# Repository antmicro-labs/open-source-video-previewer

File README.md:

# open-source-video-previewer
Project purpose
Developing video in/out overlay device, that will be able to record, process, stream further and allow to modificate processing parameters.

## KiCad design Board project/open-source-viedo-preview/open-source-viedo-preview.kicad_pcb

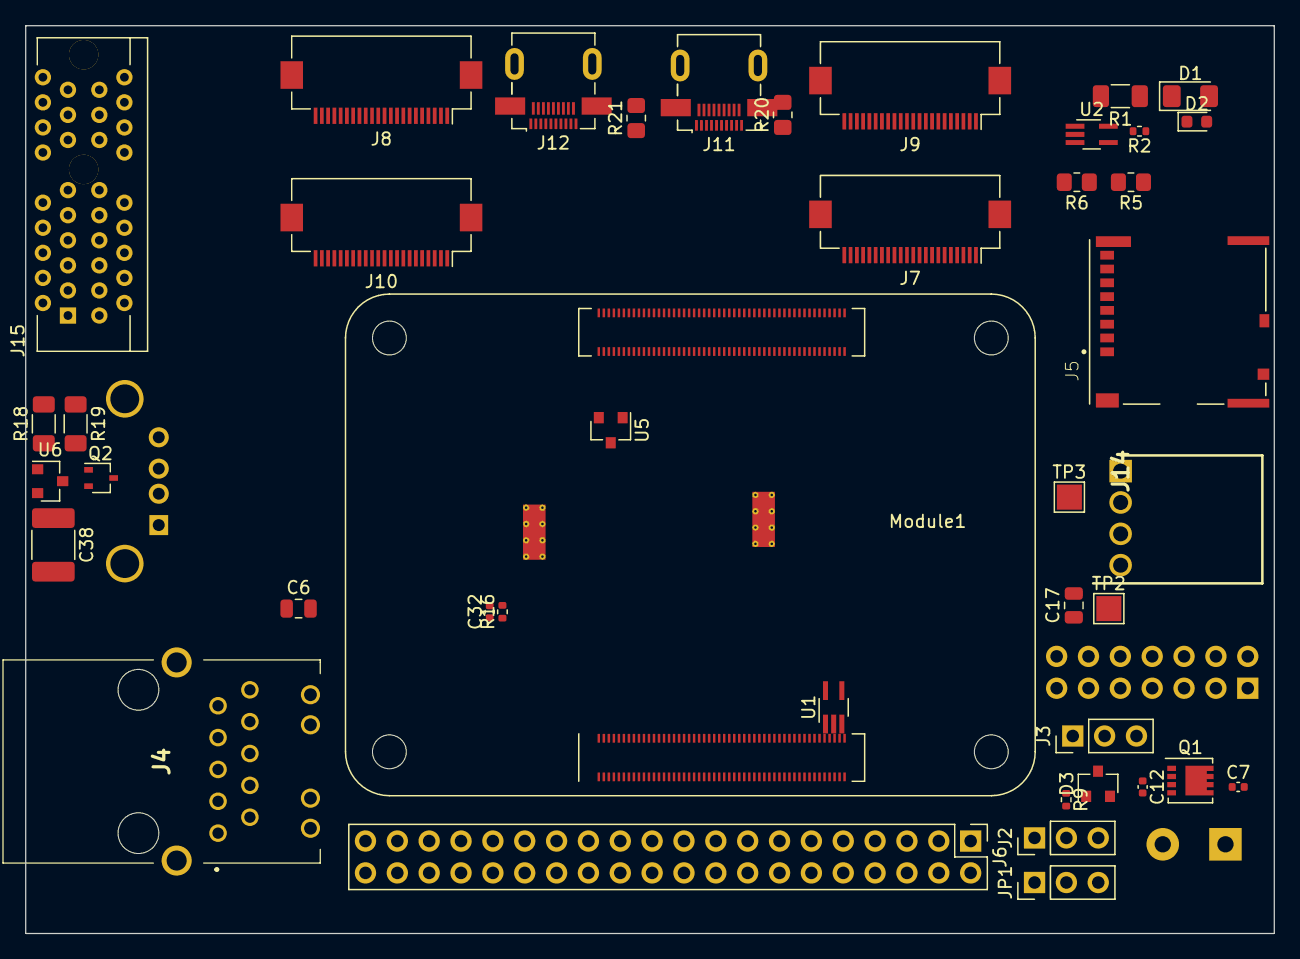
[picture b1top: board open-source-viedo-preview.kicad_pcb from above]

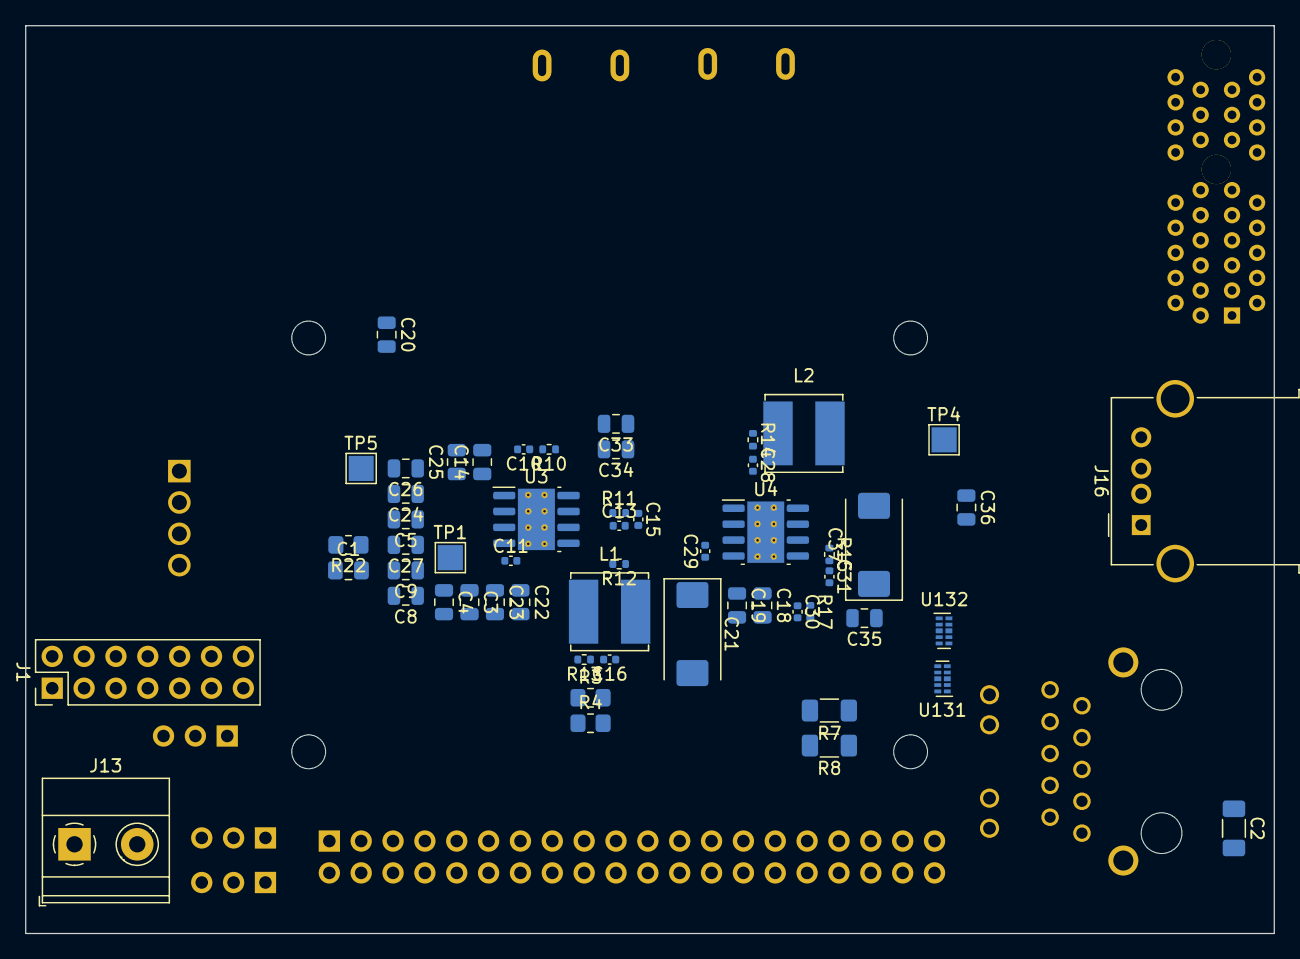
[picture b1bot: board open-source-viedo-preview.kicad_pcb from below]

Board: 4 copper layers, 99.6 x 72.4 mm, 98 parts (56 on the bottom side), 145 nets, no tracks yet.

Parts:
C1: 10u; C_0805_2012Metric_Pad1.18x1.45mm_HandSolder
C2: 10n; C_1206_3216Metric_Pad1.33x1.80mm_HandSolder
C3, C4, C5, C6, C8, C9, C14, C22, C23, C24, C25, C26, C27: 10u 35v; C_0805_2012Metric
C7: 100n 100v; C_0402_1005Metric
C10, C11, C12, C28, C29: 100n; C_0402_1005Metric
C13, C16, C30, C32: nf; C_0402_1005Metric
C15, C31: 1.2nF; C_0402_1005Metric
C17, C18, C19, C20, C33, C34, C35, C36: 10u; C_0805_2012Metric
C21, C37: 100uF; CP_EIA-7343-31_Kemet-D
C38: 4u7; C_1812_4532Metric_Pad1.57x3.40mm_HandSolder
D1: Green LED; LED_1206_3216Metric_Pad1.42x1.75mm_HandSolder
D2: LED Red; LED_0603_1608Metric
D3: MMBZ5242BLT3G; D_SOT-23_ANK
J1: Conn_02x07_Odd_Even; PinHeader_2x07_P2.54mm_Vertical
J2, J3: Conn_01x03; PinHeader_1x03_P2.54mm_Vertical
J4: 7499110124
J5: Micro_SD_Card_Det; SDCARD_MOLEX_503398-1892
J6: Conn_02x20_Odd_Even; PinHeader_2x20_P2.54mm_Vertical
J7, J8, J9, J10: Conn_01x22_Female; Hirose_FH12-22S-0.5SH_1x22-1MP_P0.50mm_Horizontal
J11, J12: HDMI_A_1.4; HDMI_Micro-D_Molex_46765-2x0x
J13: Screw_Terminal_01x02; TerminalBlock_Phoenix_MKDS-1,5-2_1x02_P5.00mm_Horizontal
J14: AMP171826-4; SHDRRA4W69P0X250_1X4_1000X1350X670P
J15: 10018783-11200TLF; PCIex1-36
J16: USB_OTG; USB_A_Molex_67643_Horizontal
JP1: Jumper_NC_Dual; PinHeader_1x03_P2.54mm_Vertical
L1, L2: SRN6045TA-3R3Y; L_Bourns_SRN6045TA
Module1: ComputeModule4-CM4; Raspberry-Pi-4-Compute-Module
Q1: DMP3013SFV-7; Diodes_PowerDI3333-8
Q2: BSS138PW; SOT-323_SC-70
R1: 1k; R_1206_3216Metric_Pad1.30x1.75mm_HandSolder
R2: 1k; R_0402_1005Metric
R3, R4: 1k8; R_0805_2012Metric_Pad1.20x1.40mm_HandSolder
R5, R6: R; R_0805_2012Metric_Pad1.20x1.40mm_HandSolder
R7, R8: 220; R_1206_3216Metric_Pad1.30x1.75mm_HandSolder
R9, R12, R15: 12K 1%; R_0402_1005Metric
R10, R14: 10R; R_0402_1005Metric
R11: 20K 1%; R_0402_1005Metric
R13: 2.2K 1%; R_0402_1005Metric
R16: 47K 1%; R_0402_1005Metric
R17: 15K 1%; R_0402_1005Metric
R18: 10k; R_1206_3216Metric_Pad1.30x1.75mm_HandSolder
R19: 2k; R_1206_3216Metric_Pad1.30x1.75mm_HandSolder
R20, R21, R22: 0R; R_0805_2012Metric_Pad1.20x1.40mm_HandSolder
TP1, TP2, TP3, TP4, TP5: TestPoint; TestPoint_Pad_2.0x2.0mm
U1, U2: 74LVC1G07; SOT-353_SC-70-5_Handsoldering
U3, U4: AP64501SP-13; SOIC-8-1EP_3.9x4.9mm_P1.27mm_EP2.95x4.9mm_Mask2.71x3.4mm_Th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
U5, U6: TPD2E009DBZR; SOT-23
U131, U132: TPD4EUSB30; USON-10_2.5x1.0mm_P0.5mm

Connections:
+1V8: JP1.3, Module1.88 (+1.8v_(Output)), Module1.90 (+1.8v_(Output))
+3V3: C16.1, C17.1, C18.1, C19.1, C20.1, C21.1, D1.2 (A), D2.2 (A), J6.1, J6.2, J6.4, J6.7, J6.17, J7.22, J8.22, J9.22, J10.22, J14.4, JP1.1, L1.2, Module1.54 (GPIO4), Module1.77 (+5v_(Input)), Module1.79 (+5v_(Input)), Module1.81 (+5v_(Input)), Module1.83 (+5v_(Input)), Module1.84 (+3.3v_(Output)), Module1.85 (+5v_(Input)), Module1.86 (+3.3v_(Output)), Module1.87 (+5v_(Input)), R5.1, R7.2, R8.2, R12.1, R20.1, R21.1, R22.1, TP2.1, U1.5 (VCC), U2.5 (VCC)
+12V: C3.1, C4.1, C5.1, C6.1, C8.1, C9.1, C12.1, C14.1, C22.1, C23.1, C24.1, C25.1, C26.1, C27.1, D3.1 (K), J14.1, J15.A2 (+12V), J15.A3 (+12V), J15.B1 (+12v), J15.B2 (+12v), J15.B3 (+12v), Q1.1 (S), Q1.2 (S), Q1.3 (S), TP1.1, U3.2 (VIN), U3.3 (EN), U4.2 (VIN), U4.3 (EN)
/pcie/+3.3v: C32.1, C33.1, C34.1, C35.1, C36.1, C37.1, J15.A5 (TCK), J15.A6 (TDI), J15.A8 (TMS), J15.A9 (+3.3V), J15.A10 (+3.3V), J15.B8 (+3.3v), J15.B9 (nTRST), J15.B10 (+3.3vAUX), L2.2, R16.1, TP4.1
/pcie/PCIE_CLK_N: J15.A14 (REFCLK-), Module1.112 (PCIe_CLK_N)
/pcie/PCIE_CLK_P: J15.A13 (REFCLK+), Module1.110 (PCIe_CLK_P)
/pcie/PCIE_CLK_nREQ: J15.B12 (nCLKREQ), Module1.102 (PCIe_CLK_nREQ)
/pcie/PCIE_RX_N: J15.A16 (PERP0), Module1.118 (PCIe_RX_N)
/pcie/PCIE_RX_P: J15.A17 (PERN0), Module1.116 (PCIe_RX_P)
/pcie/PCIE_TX_N: J15.B14 (PETP0), Module1.124 (PCIe_TX_N)
/pcie/PCIE_TX_P: J15.B15 (PETN0), Module1.122 (PCIe_TX_P)
/pcie/PCIE_nRST: J15.A11 (nPERST), Module1.109 (PCIe_nRST)
/usb-otg/USB2_N: J16.2 (D-), Module1.103 (USB2_N), U5.2 (D-)
/usb-otg/USB2_P: J16.3 (D+), Module1.105 (USB2_P), U5.1 (D+)
/usb-otg/USBOTG: Module1.101 (USB_OTG_ID), Q2.3 (D)
/video_previewGPIO/AIN0: J1.5, Module1.94 (AnalogIP0)
/video_previewGPIO/AIN1: J1.6, Module1.96 (AnalogIP1)
/video_previewGPIO/BT_nDis: J2.3, Module1.91 (BT_nDisable)
/video_previewGPIO/CAM_GPIO: J7.17, J8.17, Module1.97 (Camera_GPIO)
/video_previewGPIO/EEPROM_nWP: J1.4, Module1.20 (EEPROM_nWP)
/video_previewGPIO/ETH_LED0: J4.12 (K_GREEN), Module1.15 (Ethernet_nLED3(3.3v))
/video_previewGPIO/ETH_LED1: J4.14 (A/K_GREEN/YELLOW_2), Module1.17 (Ethernet_nLED2(3.3v))
/video_previewGPIO/ETH_TRD0_N: J4.1 (D0-), Module1.10 (Ethernet_Pair0_N), U131.2 (D1-)
/video_previewGPIO/ETH_TRD0_P: J4.2 (D0+), Module1.12 (Ethernet_Pair0_P), U131.1 (D1+)
/video_previewGPIO/ETH_TRD1_N: J4.3 (D1-), Module1.6 (Ethernet_Pair1_N), U131.5 (D2-)
/video_previewGPIO/ETH_TRD1_P: J4.4 (D1+), Module1.4 (Ethernet_Pair1_P), U131.4 (D2+)
/video_previewGPIO/ETH_TRD2_N: J4.7 (D2-), Module1.9 (Ethernet_Pair2_N), U132.2 (D1-)
/video_previewGPIO/ETH_TRD2_P: J4.8 (D2+), Module1.11 (Ethernet_Pair2_P), U132.1 (D1+)
/video_previewGPIO/ETH_TRD3_N: J4.9 (D3-), Module1.5 (Ethernet_Pair3_N), U132.5 (D2-)
/video_previewGPIO/ETH_TRD3_P: J4.10 (D3+), Module1.3 (Ethernet_Pair3_P), U132.4 (D2+)
/video_previewGPIO/GLOBAL_EN: J1.14, J3.1, Module1.99 (Global_EN)
/video_previewGPIO/GPIO2: J6.3, Module1.58 (GPIO2)
/video_previewGPIO/GPIO3: J6.5, Module1.56 (GPIO3)
/video_previewGPIO/GPIO5: J6.29, Module1.34 (GPIO5)
/video_previewGPIO/GPIO8: J6.24, Module1.39 (GPIO8)
/video_previewGPIO/GPIO9: J6.21, Module1.40 (GPIO9)
/video_previewGPIO/GPIO10: J6.19, Module1.44 (GPIO10)
/video_previewGPIO/GPIO11: J6.23, Module1.38 (GPIO11)
/video_previewGPIO/GPIO12: J6.32, Module1.31 (GPIO12)
/video_previewGPIO/GPIO13: J6.33, Module1.28 (GPIO13)
/video_previewGPIO/GPIO17: J6.11, Module1.50 (GPIO17)
/video_previewGPIO/GPIO19: J6.35, Module1.26 (GPIO19)
/video_previewGPIO/GPIO20: J6.38, Module1.27 (GPIO20)
/video_previewGPIO/GPIO23: J6.16, Module1.47 (GPIO23)
/video_previewGPIO/GPIO24: J6.18, Module1.45 (GPIO24)
/video_previewGPIO/GPIO25: J6.22, Module1.41 (GPIO25)
/video_previewGPIO/GPIO26: J6.37, Module1.24 (GPIO26)
/video_previewGPIO/GPIO27: J6.13, Module1.48 (GPIO27)
/video_previewGPIO/GPIO_VREF: JP1.2, Module1.78 (GPIO_VREF(1.8v/3.3v_Input)), R3.1, R4.1
/video_previewGPIO/ID_SC: J6.28, Module1.35 (ID_SC), R4.2
/video_previewGPIO/ID_SD: J6.27, Module1.36 (ID_SD), R3.2
/video_previewGPIO/RUN_PG: J3.3, Module1.92 (RUN_PG), U1.2
/video_previewGPIO/Reserved: Module1.76 (Reserved), R6.1
/video_previewGPIO/SCL0: J8.20, J9.20, Module1.80 (SCL0)
/video_previewGPIO/SDA0: J8.21, J9.21, Module1.82 (SDA0)
/video_previewGPIO/SD_CLK: J5.5 (CLK), Module1.57 (SD_CLK)
/video_previewGPIO/SD_CMD: J5.3 (CMD), Module1.62 (SD_CMD)
/video_previewGPIO/SD_DATA0: J5.7 (DAT0), Module1.63 (SD_DAT0)
/video_previewGPIO/SD_DATA1: J5.8 (DAT1), Module1.67 (SD_DAT1)
/video_previewGPIO/SD_DATA2: J5.1 (DAT2), Module1.69 (SD_DAT2)
/video_previewGPIO/SD_DATA3: J5.2 (DAT3/CD), Module1.61 (SD_DAT3)
/video_previewGPIO/SYNC_IN: J1.8, Module1.16 (Ethernet_SYNC_IN(1.8v))
/video_previewGPIO/SYNC_OUT: J1.9, Module1.18 (Ethernet_SYNC_OUT(1.8v))
/video_previewGPIO/WL_nDIS: J2.1, Module1.89 (WiFi_nDisable)
/video_previewGPIO/nPWR_LED: Module1.95 (nPI_LED_PWR), U2.2
/video_previewGPIO/nRPIBOOT: J1.2, Module1.93 (nRPIBOOT)
/video_preview_HighSpeed/CAM0_D0_P: J7.3, Module1.130 (CAM0_D0_P)
/video_preview_HighSpeed/CAM0_D1_N: J7.5, Module1.134 (CAM0_D1_N)
/video_preview_HighSpeed/CAM0_D1_P: J7.6, Module1.136 (CAM0_D1_P)
/video_preview_HighSpeed/CAM1_C_N: J8.8, Module1.127 (CAM1_C_N)
/video_preview_HighSpeed/CAM1_C_P: J8.9, Module1.129 (CAM1_C_P)
/video_preview_HighSpeed/CAM1_D0_N: J8.2, Module1.115 (CAM1_D0_N)
/video_preview_HighSpeed/CAM1_D0_P: J8.3, Module1.117 (CAM1_D0_P)
/video_preview_HighSpeed/CAM1_D1_N: J8.5, Module1.121 (CAM1_D1_N)
/video_preview_HighSpeed/CAM1_D1_P: J8.6, Module1.123 (CAM1_D1_P)
/video_preview_HighSpeed/CAM1_D2_N: J8.11, Module1.133 (CAM1_D2_N)
/video_preview_HighSpeed/CAM1_D2_P: J8.12, Module1.135 (CAM1_D2_P)
/video_preview_HighSpeed/CAM1_D3_N: J8.14, Module1.139 (CAM1_D3_N)
/video_preview_HighSpeed/CAM1_D3_P: J8.15, Module1.141 (CAM1_D3_P)
/video_preview_HighSpeed/DSI0_C_N: J10.8, Module1.169 (DSI0_C_N)
/video_preview_HighSpeed/DSI0_C_P: J10.9, Module1.171 (DSI0_C_P)
/video_preview_HighSpeed/DSI0_D0_N: J10.2, Module1.157 (DSI0_D0_N)
/video_preview_HighSpeed/DSI1_C_N: J9.8, Module1.187 (DSI1_C_N)
/video_preview_HighSpeed/DSI1_C_P: J9.9, Module1.189 (DSI1_C_P)
/video_preview_HighSpeed/DSI1_D0_N: J9.2, Module1.175 (DSI1_D0_N)
/video_preview_HighSpeed/DSI1_D1_N: J9.5, Module1.181 (DSI1_D1_N)
/video_preview_HighSpeed/DSI1_D1_P: J9.6, Module1.183 (DSI1_D1_P)
/video_preview_HighSpeed/DSI1_D2_N: J9.11, Module1.193 (DSI1_D2_N)
/video_preview_HighSpeed/DSI1_D2_P: J9.12, Module1.195 (DSI1_D2_P)
/video_preview_HighSpeed/DSI1_D3_N: J9.14, Module1.194 (DSI1_D3_N)
/video_preview_HighSpeed/DSI1_D3_P: J9.15, Module1.196 (DSI1_D3_P)
/video_preview_HighSpeed/HDMI0_CEC: J11.13 (CEC), Module1.151 (HDMI0_CEC)
/video_preview_HighSpeed/HDMI0_CK_N: J11.12 (CK-), Module1.190 (HDMI0_CLK_N)
/video_preview_HighSpeed/HDMI0_CK_P: J11.10 (CK+), Module1.188 (HDMI0_CLK_P)
/video_preview_HighSpeed/HDMI0_D0_P: J11.7 (D0+), Module1.182 (HDMI0_TX0_P)
/video_preview_HighSpeed/HDMI0_D1_N: J11.6 (D1-), Module1.178 (HDMI0_TX1_N)
/video_preview_HighSpeed/HDMI0_D1_P: J11.4 (D1+), Module1.176 (HDMI0_TX1_P)
/video_preview_HighSpeed/HDMI0_D2_P: J11.1 (D2+), J11.3 (D2-), Module1.170 (HDMI0_TX2_P)
/video_preview_HighSpeed/HDMI0_HOTPLUG: J11.19 (HPD/HEAC-), Module1.153 (HDMI0_HOTPLUG)
/video_preview_HighSpeed/HDMI0_SCL: J11.15 (SCL), Module1.200 (HDMI0_SCL)
/video_preview_HighSpeed/HDMI0_SDA: J11.16 (SDA), Module1.199 (HDMI0_SDA)
/video_preview_HighSpeed/HDMI1_CEC: J12.13 (CEC), Module1.149 (HDMI1_CEC)
/video_preview_HighSpeed/HDMI1_CK_N: J12.12 (CK-), Module1.166 (HDMI1_CLK_N)
/video_preview_HighSpeed/HDMI1_CK_P: J12.10 (CK+), Module1.164 (HDMI1_CLK_P)
/video_preview_HighSpeed/HDMI1_D0_P: J12.7 (D0+), Module1.158 (HDMI1_TX0_P)
/video_preview_HighSpeed/HDMI1_D1_N: J12.6 (D1-), Module1.154 (HDMI1_TX1_N)
/video_preview_HighSpeed/HDMI1_D1_P: J12.4 (D1+), Module1.152 (HDMI1_TX1_P)
/video_preview_HighSpeed/HDMI1_D2_P: J12.1 (D2+), J12.3 (D2-)
/video_preview_HighSpeed/HDMI1_HOTPLUG: J12.19 (HPD/HEAC-), Module1.143 (HDMI1_HOTPLUG)
/video_preview_HighSpeed/HDMI1_SCL: J12.15 (SCL), Module1.147 (HDMI1_SCL)
/video_preview_HighSpeed/HDMI1_SDA: J12.16 (SDA), Module1.145 (HDMI1_SDA)
/video_preview_HighSpeed/SCL1: J7.20, J10.20
/video_preview_HighSpeed/SDA1: J7.21, J10.21
GND: C1.2, C2.2, C3.2, C4.2, C5.2, C6.2, C7.2, C8.2, C9.2, C11.2, C13.2, C14.2, C15.2, C17.2, C18.2, C19.2, C20.2, C21.2, C22.2, C23.2, C24.2, C25.2, C26.2, C27.2, C29.2, C30.2, C31.2, C33.2, C34.2, C35.2, C36.2, C37.2, C38.2, J1.1, J1.3, J1.7, J1.10, J1.12, J2.2, J3.2, J4.15 (Shield), J4.16 (Shield), J5.6 (VSS), J5.11 (SHIELD), J6.6, J6.8, J6.9, J6.10, J6.12, J6.14, J6.15, J6.20, J6.25, J6.26, J6.30, J6.31, J6.34, J6.36, J6.39, J6.40, J7.1, J7.4, J7.7, J7.10, J7.13, J7.16, J8.1, J8.4, J8.7, J8.10, J8.13, J8.16, J8.19, J9.1, J9.4, J9.7, J9.10, J9.13, J9.16, J9.19, J10.1, J10.4, J10.7, J10.10, J10.13, J10.16, J10.19, J11.2 (D2S), J11.5 (D1S), J11.8 (D0S), J11.11 (CKS), J11.17 (GND), J11.SH, J12.2 (D2S), J12.5 (D1S), J12.8 (D0S), J12.11 (CKS), J12.17 (GND), J12.SH, J13.1, J14.2, J14.3, J15.A4 (GND), J15.A12 (GND), J15.A15 (GND), J15.A18 (GND), J15.B4 (GND), J15.B7 (GND), J15.B13 (GND), J15.B16 (GND), J15.B18 (GND), J16.5 (GND), Module1.1 (GND), Module1.2 (GND), Module1.7 (GND), Module1.8 (GND), Module1.13 (GND), Module1.14 (GND), Module1.22 (GND), Module1.23 (GND), Module1.25 (GPIO21), Module1.29 (GPIO16), Module1.30 (GPIO6), Module1.32 (GND), Module1.33 (GND), Module1.37 (GPIO7), Module1.42 (GND), Module1.43 (GND), Module1.46 (GPIO22), Module1.49 (GPIO18), Module1.51 (GPIO15), Module1.52 (GND), Module1.53 (GND), Module1.55 (GPIO14), Module1.59 (GND), Module1.60 (GND), Module1.65 (GND), Module1.66 (GND), Module1.71 (GND), Module1.74 (GND), Module1.98 (GND), Module1.107 (GND), Module1.108 (GND), Module1.113 (GND), Module1.114 (GND), Module1.119 (GND), Module1.120 (GND), Module1.125 (GND), Module1.126 (GND), Module1.131 (GND), Module1.132 (GND), Module1.137 (GND), Module1.138 (GND), Module1.144 (GND), Module1.150 (GND), Module1.155 (GND), Module1.156 (GND), Module1.161 (GND), Module1.162 (GND), Module1.167 (GND), Module1.168 (GND), Module1.173 (GND), Module1.174 (GND), Module1.179 (GND), Module1.180 (GND), Module1.185 (GND), Module1.186 (GND), Module1.191 (GND), Module1.192 (GND), Module1.197 (GND), Module1.198 (GND), Q2.2 (S), R9.2, R13.2, R17.2, R19.2, TP3.1, TP5.1, U1.3 (GND), U2.3 (GND), U3.7 (GND), U3.9 (EP), U4.7 (GND), U4.9 (EP), U5.3 (GND), U6.3 (GND), U131.3 (GND), U131.8 (GND), U132.3 (GND), U132.8 (GND)
unnamed: C1.1, J5.4 (VDD), R22.2
unnamed: C2.1, J4.5 (CTREF), J4.6 (CTREF)
unnamed: C7.1, J13.2, Q1.5 (D)
unnamed: C10.1, R10.2
unnamed: C10.2, U3.1 (BST)
unnamed: C11.1, U3.4 (SS)
unnamed: C12.2, D3.2 (A), Q1.4 (G), R9.1
unnamed: C13.1, R11.1, U3.6 (COMP)
unnamed: C15.1, R11.2
unnamed: C16.2, R12.2, R13.1, U3.5 (FB)
unnamed: C28.1, R14.2
unnamed: C28.2, U4.1 (BST)
unnamed: C29.1, U4.4 (SS)
unnamed: C30.1, R15.1, U4.6 (COMP)
unnamed: C31.1, R15.2
unnamed: C32.2, R16.2, R17.1, U4.5 (FB)
unnamed: C38.1, J16.1 (VBUS), R18.1, U6.1 (D+), U6.2 (D-)
unnamed: D1.1 (K), R1.1
unnamed: D2.1 (K), R2.1
unnamed: J1.13, U1.4
unnamed: J4.11 (A_GREEN), R7.1
unnamed: J4.13 (A/K_GREEN/YELLOW_1), R8.1
unnamed: J5.9 (DET_B), R6.2
unnamed: J5.10 (DET_A), R5.2
unnamed: J11.18 (+5V), R20.2
unnamed: J12.18 (+5V), R21.2
unnamed: L1.1, R10.1, U3.8 (SW)
unnamed: L2.1, R14.1, U4.8 (SW)
unnamed: Module1.21 (PI_nLED_Activity), R1.2
unnamed: Q2.1 (G), R18.2, R19.1
unnamed: R2.2, U2.4

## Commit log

2020-11-06 Initial - readme
2020-12-16 Initial commit. Added RPI CM4 port (part A) and Ethernet
2020-12-17 Element library added
2020-12-17 40 GPIOs pins added
2021-01-07 Pins 51-100 and HighSpeed part with cam connector added.
2021-01-26 150-200 pin's created by Mateusz
2021-02-11 PSU added
2021-02-21 pin 101-150
2021-03-08 Imporoved electrical schematic
2021-03-08 Added SD Slot Card
2021-03-09 added 3.3v power supply for PCIe
2021-03-09 ERC error repaired
2021-03-10 added ESD protection on Ethernet lines and change net labels for this interface
2021-03-22 Footprints added (without HDMI)
2021-03-23 First element placemed on PCB
2021-03-29 Add HDMI and some power supply paths
2021-03-29 Add PCB file to commit
2021-09-03 Elements new placement
